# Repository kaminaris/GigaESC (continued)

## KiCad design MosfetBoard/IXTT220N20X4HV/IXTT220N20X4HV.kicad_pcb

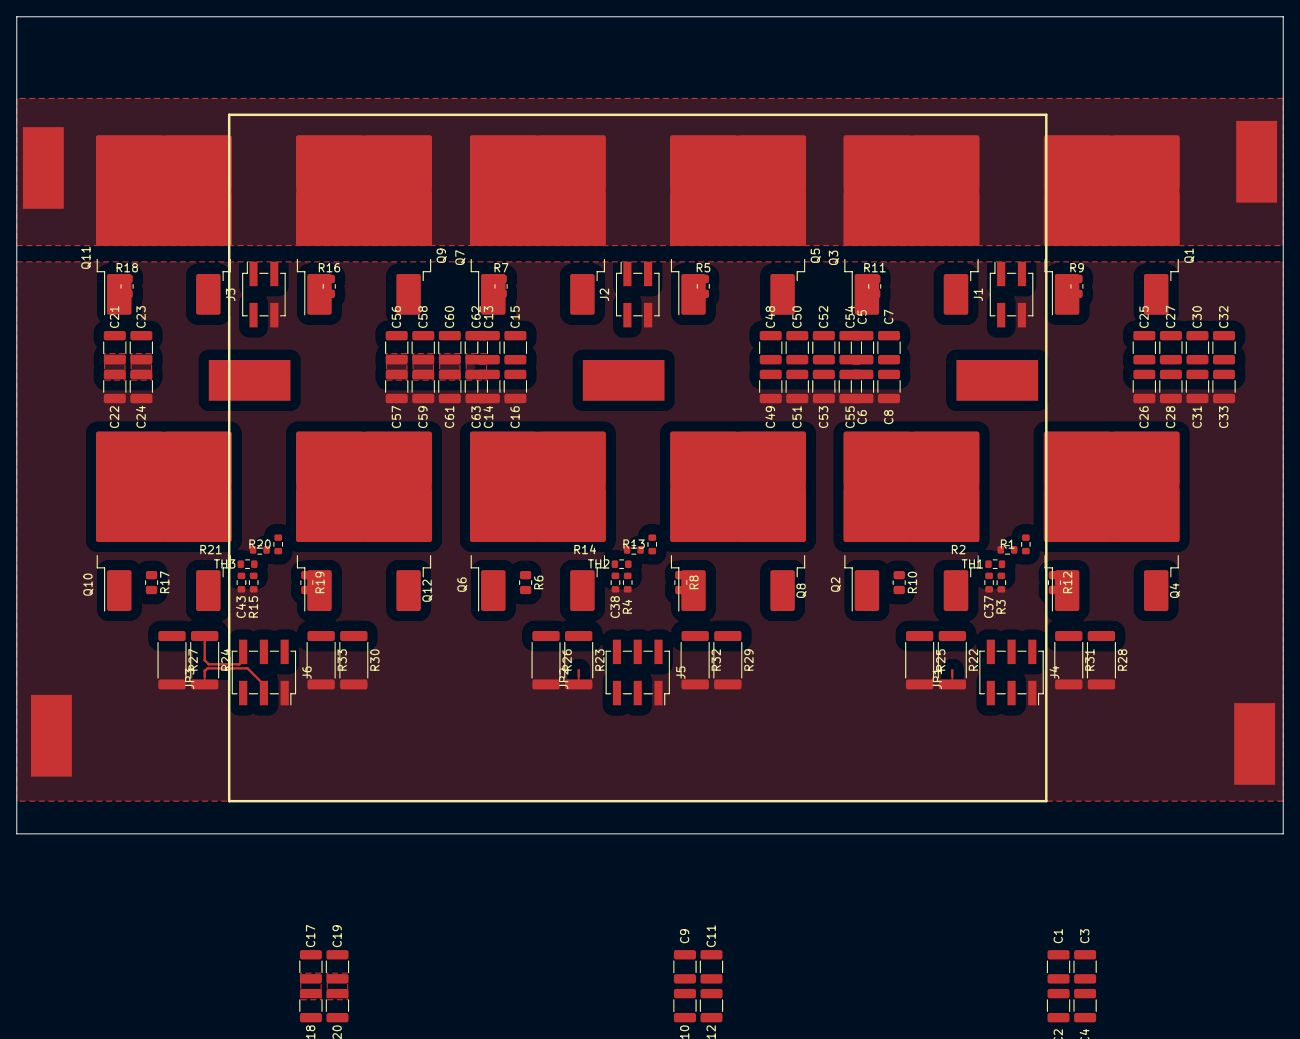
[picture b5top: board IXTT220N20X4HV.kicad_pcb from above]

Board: 2 copper layers, 155.0 x 100.0 mm, 115 parts (0 on the bottom side), 62 nets.

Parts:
C1, C2, C3, C4, C5, C6, C7, C8, C9, C10, C11, C12, C13, C14, C15, C16, C17, C18, C19, C20, C21, C22, C23, C24, C25, C26, C27, C28, C30, C31, C32, C33, C48, C49, C50, C51, C52, C53, C54, C55, C56, C57, C58, C59, C60, C61, C62, C63: 10u 100V; C_1210_3225Metric
C37, C38, C43: 1u; C_0603_1608Metric_L
J1, J2, J3: DRIVER1; PinSocket_2x02_P2.54mm_Vertical_SMD
J4, J5, J6: PhaseConn; PinSocket_2x03_P2.54mm_Vertical_SMD
J7, J10, J11: PhasePad; SolderWirePad_1x01_SMD_5x10mm
J8: BATT+Conn1; SolderWirePad_1x01_SMD_5x10mm
J9: BATT-Conn1; SolderWirePad_1x01_SMD_5x10mm
J13: BATT+Conn2; SolderWirePad_1x01_SMD_5x10mm
J14: BATT-Conn2; SolderWirePad_1x01_SMD_5x10mm
JP1, JP2, JP3: DummyJumper; SolderJumper0.3mm
Q1, Q2, Q3, Q4, Q5, Q6, Q7, Q8, Q9, Q10, Q11, Q12: IXTT220N20X4HV; TO-268-2
R1, R13, R20: 150k; R_0603_1608Metric
R2, R14, R21: 2.7k; R_0603_1608Metric
R3, R4, R15: 10k; R_0603_1608Metric
R5, R6, R7, R8, R9, R10, R11, R12, R16, R17, R18, R19: 2.2; R_0805_2012Metric
R22, R23, R24, R25, R26, R27, R28, R29, R30, R31, R32, R33: 0.5m; R_2512_6332Metric
TH1, TH2, TH3: NCP18XH103F03RB; R_0603_1608Metric

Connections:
+BATT: C1.1, C3.1, C5.1, C7.1, C9.1, C11.1, C13.1, C15.1, C17.1, C19.1, C21.1, C23.1, C25.1, C27.1, C30.1, C32.1, C48.1, C50.1, C52.1, C54.1, C56.1, C58.1, C60.1, C62.1, J8.1, J13.1, Q1.2 (D), Q3.2 (D), Q5.2 (D), Q7.2 (D), Q9.2 (D), Q11.2 (D)
-BATT: C2.2, C4.2, C6.2, C8.2, C10.2, C12.2, C14.2, C16.2, C18.2, C20.2, C22.2, C24.2, C26.2, C28.2, C31.2, C33.2, C37.2, C38.2, C43.2, C49.2, C51.2, C53.2, C55.2, C57.2, C59.2, C61.2, C63.2, J1.4, J2.4, J3.4, J4.1, J5.1, J6.1, J9.1, J14.1, JP1.1 (A), JP2.1 (A), JP3.1 (A), R2.2, R3.2, R4.2, R14.2, R15.2, R21.2, R22.2, R23.2, R24.2, R25.2, R26.2, R27.2, R28.2, R29.2, R30.2, R31.2, R32.2, R33.2
/PhaseMosfets1/3.3V_IN: J4.5, TH1.1
/PhaseMosfets1/MOS_TEMP: C37.1, J4.4, R3.1, TH1.2
/PhaseMosfets1/PH: J1.1, R9.1, R11.1
/PhaseMosfets1/PHASE: J1.3, J7.1, Q1.3 (S), Q2.2 (D), Q3.3 (S), Q4.2 (D), R1.1
/PhaseMosfets1/PL: J1.2, R10.1, R12.1
/PhaseMosfets1/SH+: J4.6, Q2.3 (S), Q4.3 (S), R22.1, R25.1, R28.1, R31.1
/PhaseMosfets1/SH-: J4.3, JP1.2 (B)
/PhaseMosfets1/V_SENSE: J4.2, R1.2, R2.1
/PhaseMosfets2/3.3V_IN: J5.5, TH2.1
/PhaseMosfets2/MOS_TEMP: C38.1, J5.4, R4.1, TH2.2
/PhaseMosfets2/PH: J2.1, R5.1, R7.1
/PhaseMosfets2/PHASE: J2.3, J10.1, Q5.3 (S), Q6.2 (D), Q7.3 (S), Q8.2 (D), R13.1
/PhaseMosfets2/PL: J2.2, R6.1, R8.1
/PhaseMosfets2/SH+: J5.6, Q6.3 (S), Q8.3 (S), R23.1, R26.1, R29.1, R32.1
/PhaseMosfets2/SH-: J5.3, JP2.2 (B)
/PhaseMosfets2/V_SENSE: J5.2, R13.2, R14.1
/PhaseMosfets3/3.3V_IN: J6.5, TH3.1
/PhaseMosfets3/MOS_TEMP: C43.1, J6.4, R15.1, TH3.2
/PhaseMosfets3/PH: J3.1, R16.1, R18.1
/PhaseMosfets3/PHASE: J3.3, J11.1, Q9.3 (S), Q10.2 (D), Q11.3 (S), Q12.2 (D), R20.1
/PhaseMosfets3/PL: J3.2, R17.1, R19.1
/PhaseMosfets3/SH+: J6.6, Q10.3 (S), Q12.3 (S), R24.1, R27.1, R30.1, R33.1
/PhaseMosfets3/SH-: J6.3, JP3.2 (B)
/PhaseMosfets3/V_SENSE: J6.2, R20.2, R21.1
unnamed: C1.2, C2.1
unnamed: C3.2, C4.1
unnamed: C5.2, C6.1
unnamed: C7.2, C8.1
unnamed: C9.2, C10.1
unnamed: C11.2, C12.1
unnamed: C13.2, C14.1
unnamed: C15.2, C16.1
unnamed: C17.2, C18.1
unnamed: C19.2, C20.1
unnamed: C21.2, C22.1
unnamed: C23.2, C24.1
unnamed: C25.2, C26.1
unnamed: C27.2, C28.1
unnamed: C30.2, C31.1
unnamed: C32.2, C33.1
unnamed: C48.2, C49.1
unnamed: C50.2, C51.1
unnamed: C52.2, C53.1
unnamed: C54.2, C55.1
unnamed: C56.2, C57.1
unnamed: C58.2, C59.1
unnamed: C60.2, C61.1
unnamed: C62.2, C63.1
unnamed: Q1.1 (G), R9.2
unnamed: Q2.1 (G), R10.2
unnamed: Q3.1 (G), R11.2
unnamed: Q4.1 (G), R12.2
unnamed: Q5.1 (G), R5.2
unnamed: Q6.1 (G), R6.2
unnamed: Q7.1 (G), R7.2
unnamed: Q8.1 (G), R8.2
unnamed: Q9.1 (G), R16.2
unnamed: Q10.1 (G), R17.2
unnamed: Q11.1 (G), R18.2
unnamed: Q12.1 (G), R19.2
